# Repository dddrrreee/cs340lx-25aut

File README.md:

### CS340lx: (even more) advanced systems labs

Official description:
  - This is an implementation-heavy, lab-based class that continues the
    topics from CS240LX. The labs will be more specialized, with an emphasis
    on research-worthy topics and techniques. The class format will follow
    CS240LX: two labs, twice a week, along with a set of research papers
    for context.

Context:
 - Final class in the 140e/240lx pipeline (as of rn :).
 - We only offer it every few years when there is an unusual 
   group.  Lots of great alumni!
 - This is the 3rd offering.
 - Joe graduated, but we have Joseph as a variant!

Structure:
 - 140e and 240lx have to fulfill class requirements, so content somewhat
   constrained.  
 - 340lx we build whatever seems interesting --- only rule is we build and
   you have a working example of a cool trick or deep method every lab.

   In general: we go broader on fun stuff (devices), go deeper on
   interesting stuff than the simple examples in previous labs.  
 - One fantastic difference: Around half of the labs are usually
   student-written.  You have already suffered through over 30 labs
   as consumers, so now is your chance to buld the labs you would have 
   wanted.  

   This is my favorite part of the class.  I always learn alot.  The new
   labs give tricks useful for 140e/240lx.  And, as we saw, (eg Stuart's
   elf lab) these labs can >>> better than our staff ones :)

What's the big picture goal: 
 - Do a bunch of cool devices for fun.  

   Since we have a limited enrollment, can afford more expensive ones
   (lidar, screens, kilometer capable LoRa RF)

 - Do a bunch of new sbc's --- arm, riscv, whatever.  

   Often bootup is
   the most difficult part, so it's good to have a portfolio.  Also once
   you see more, you start to get a feel for what is an arbitrary choice

   and which have a
 - Now that you have a solid grasp of low-level hardware and code, we 
   build more advanced stuff, and go much deeper.    

   From the past: build a riscv simulator that can simulate itself and
   is register equivalent with the hardware.

 - Build simple versions of advanced techniques in other areas.
   Some examples from the past:
     - Build a SAT solver (Matthew)
     - Build a constraint solver (Matthew)
     - Static analysis bug finders (Matthew and Manya),
     - Verilog FPGA examples (Zack)

-------------------------------------------------------------------
### Possible labs

Definite lab:
 - Parthiv's PCB lab next thursday 10/2.

Some possible good labs from 240lx final projects

 - Stuart's elf debug: use to make a real profiler.
 - Quake (sai and james): will do screen and keyboard labs
 - ox64 (Aditya et al): cheap, real riscv
 - Pi zero 2 (Benji): 4 armv7 processor, faster, still bcm2835.
 - handwriting rec (Chia-Hsiang, Irene, Kaylee, Weixin)
 - fuse?

Likely devices:
  - i2s microphone, 
  - class D amplifier + speaker
  - HDMI screen
  - Lidar
  - camera?
  - sbcs: pico 2, pico, ox64, pi zero 2

Tentative things I'd like to do (won't do all)
     - Doing Turing complete DMA (based on Max Cura's hack) - Speed up
     interrupts/exceptions by 50x.
  - a solid network boot loader that works over RF, sound, light, IR.
    It's wild to send code using sound or a blinky light.
  - A few projects putting together several devices.
    (e.g., accel controlled lights, acoustically reactive displays)
    Key: use tricks to verify the system so you're suprised if it breaks.
  - in honor of Joe: chip8 video game emulator.
  - Make a bunch of stuff really, really fast.  Fun hack is write code
    on your pi that beats
    linux/macos on your fancy modern laptop --- e.g., exceptions or 
    tiny processes so you can quickly fork 100,000 (versus crashing 
    your laptop).
  - finally build the runtime tools we were discussing: eraser race detector, 
    volatile checker.
  - do much better versions of 140e labs so can pull them in: ideally
    a simple complete OS.  definitely a better fast FAT32

The basic play: we've spend a couple quarters learning alot of low-level
stuff the hard way.  Now reap the rewards using it to build the cool
stuff.

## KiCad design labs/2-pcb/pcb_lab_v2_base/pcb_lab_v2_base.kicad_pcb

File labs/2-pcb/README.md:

# PCB (KiCAD) Lab v2 by Parthiv

## Overview
This lab will be focused on designing printed circuit boards (PCBs), which many students in 140e/240lx/340lx have found useful over the years in final projects to help reduce wiring complexity and increase hardware reliability. The focus of the lab will be on how to replace a bundle of wires with an inexpensive PCB, and not on how to actually design electrical circuits (which is a much more complicated discussion). For the most part, you can get by just connecting breakout boards together. If you want to integrate a piece of hardware without a breakout board, most datasheets will include an "application circuit" that will show you what supporting hardware is needed.

Our goal is to create a board that can plug into the Raspberry Pi GPIO header and connect to a USB to UART converter along with some RGB LEDs. To extend the lab, you'll also add in connections to a few sensors/peripherals/hardware of your choice. 

## General Keyboard Shortcuts
I assume `Ctrl` becomes `Cmd` on mac.

* `Ctrl+S`: Save (do often!)
* `Ctrl+Z`: Undo
* `Ctrl+Y`: Redo

## Step 0: Prelab

Please review [PRELAB.md](./PRELAB.md). If interested, you can also check out a previous version of the lab [here](https://github.com/dddrrreee/cs240lx-23spr/tree/main/labs/16-pcb). In the original version of the lab, we focused on designing a board with NRF24L01 wireless transceivers. You can use that board for inspiration if you'd prefer to do something a little more "batteries included".

**A mouse will be very helpful!**

## Step 1: Creating a Project

1. Open up KiCAD (either type `kicad` in your terminal or search for it in your installed applications).
2. Go to File->New Project. Select a location where you want to create the project (you can do it in this directory) and give it a name. Ensure that the box to "Create a new folder for the project" is selected. Create the project.
3. You should see a window like this:

    On the left side, you can see a file called [project_name].kicad_pcb and another file called [project_name].kicad_sch. Double clicking these will open the PCB and Schematic editors respectively. We will learn what these are in more detail.

## Step 2: Creating a Schematic

1. In the main KiCAD window, double click the .kicad_sch file to open the Schematic editor. You'll probably get a popup saying that KiCAD is being run for the first time; just use the default option to "Copy default global symbol library table". Once that's done, you will see a blank schematic:

    The schematic is where we will describe what pins of what components connect to what other pins of other components. The analog here is your `.h` file. You'll definine the connections between components (like function interfaces) but not the actual physical implementation of those connections (like the function implementations in `.c`). You should try to keep this organized if you can! I will show you some strategies on how to do this. 

    You can middle click and drag to move, or scroll up/down to zoom. Ctrl+scroll will move you left/right and shift+scroll will move you up and down, if you prefer that to middle click and drag.

2. Go to Place->Add Symbol (or type the keyboard shortcut `A`). Again, if you get a popup here, "Copy default global footprint library". In the search bar, search for the symbol `Raspberry_Pi_2_3`. Select it, then click OK to start placing the component. Place it somewhere in the middle of the schematic by clicking. If you want to move it, you can click on it, hit `M`, and then move it around, then click again to place it. You'll immediately notice that the pins are laid out quite differently from the actual physical pins on the Pi. And you'll see just one GND, 5V, and 3.3V pin, though the Pi has many. This is one of the ways that we simplify the schematic view to make it a bit easier to see what's going on. In older versions of KiCAD, you may see all of the power pins represented; if so, you can just wire them all together in the schematic (see old version of the lab).

3. Now, we will connect the power rails of the Raspberry Pi. Hit `P` to open up the power symbol menu. Search for `GND`, select it, and hit OK to start placing the ground symbol. Put it near the bottom of the Raspberry Pi symbol. Hover over the end of one of the GND pins on the Pi, then hit `W` to start drawing a wire. Note that it'll start drawing a wire from wherever your mouse was; if it was in a bad spot, you can click `Esc` to cancel drawing the wire and try again. Connect the Pi's GND pin to the GND symbol you just placed.

    Next, add power symbols for `+5V` and `+3V3` to the schematic, and connect those to the 5V and 3V3 pins of the Pi.

4. Now that we've connected the power for the Pi, let's add the RGB LEDs. We are going to use the SK6812 LEDs, which are compatible with the more common WS2812 but work with the 3.3V logic level that the Pi outputs. Technically, WS2812 require 5V logic (though we often get away with 3.3V for small chains). You can review the SK6812 datasheet in [docs/SK6812.pdf](docs/SK6812.pdf). It's a pretty short datasheet and worth looking through the whole thing.

    In the schematic view, type `A` to add a new component, then search for `SK6812`. Place a few of them down (however many you'd like)! You can also just place one, click `Esc` to get out of the add component mode, then left click and drag to select the LED you placed, then Ctrl+C/Ctrl+V to duplicate it however many times. 
    
    Something to know is VDD (or sometimes VCC) in datasheets or component pinouts refers to the positive voltage, while VSS (or VEE) refers to ground.
    
    If you read the datasheet (read the datasheet!), you'll see that the manufacturer recommends placing capacitors between the 5V supply and ground near each of the LEDs. This is a pretty common thing you'll see to help provide a more stable voltage supply to more power-hungry components. Usually, they'll specify the capacitance properly (in pF, uF, or nF), but here you can see a 3-number code of `104`. A quick search will tell you that `104` is 100nF or 0.1uF. Let's add these capacitors too; the name in the parts menu is `C`.
    
    Go ahead and connect +5V and GND sources to each of the LEDs as required (type `P` to add power sources, `W` to draw wires). When drawing wires, if you click before reaching your destination, you'll get to decide where the wire turns in the schematic view which can be helpful for organization. It's common to just have a whole bunch of power sources all over the schematic to avoid drawing long wires between them. There is an implied connection between all sources with the same label. 

    Pro-tip: you can make one LED/capacitor/wires/sources unit and then copy/paste that a few times. 

    Apply the capacitance value to the capacitors by clicking on the capacitor, then typing `E` to edit. Then in the popup window, update the value in the `Value` field. This isn't enforced in any way, it's just a note so you know what it is when you're placing the capacitors on the PCB.

    Choose a Pi pin to connect the first LED's DIN port to. I chose GPIO12 (which is incidentally pin 32). Your schematic should look something like this:

5. Now, let's create a connector for a [USB/UART converter breakout board](https://www.amazon.com/MTDELE-CP2102-Serial-Adapter-Module/dp/B0D76NNWVW) so we can plug it directly into the PCB. Unfortunately, most breakout boards won't have an associated symbol in KiCAD, but it's good practice for creating new symbols. We'll want to create a symbol to represent the logical pins that the USB/UART has. Go to Tools->Symbol Editor. You will see a blank symbol editor like this:

    On the left, you can see various symbol libraries which contain different default parts that are common enough to be included in KiCAD. We will be creating a new one.

    In the symbol editor, go to File->New Library. If you make it Project, any parts you make will only be usable in the current project. If you make it Global, you can use it in future projects. I went with Project but either is ok. Give it whatever name you want (`cs340lx_pcb`, or something).

    On the left window, find the library you created and right click on it. Then click New Symbol, and you'll see a new window pop up. See below for recommended settings.

    Click on OK and create it. 
    
    On the left of the main window (to the right of the list of libraries), right click on the grid and select Edit Grids.

    In the window that shows up, change the Fast Grid Switching: Grid 1 to 100mil/2.54mm. This helps with alignment for placing pins in the symbol. Then close this window, and type `Alt+1` to switch to the 100mil/2.54mm grid. Make sure the bottom of the symbol editor shows `grid 100`.
    
    Now that setup is done, it's time to make the symbol. On the right side of the main window, select the Draw Rectangles tool and draw a rectangle on the screen. Don't worry, you can change it later. If you want to move the auto-generated text (`J`), you can click on it (press escape to reach select mode like in the schematic editor) and hit `M` to move it. Click to place.

    Now, we will add the pins. Hit `P` to create a pin. We'll make the `GND` pin, which is pin number 4 (4th from the top of the UART) and is a Power Output. The reason we choose Output is because the entire system's power/ground is going to be generated by the UART plugged into your computer.

    Place the pin down at the bottom of the rectangle, ensuring that the circle end of the pin is facing out (this is where you'll connect wires in the schematic). Click `R` to rotate the pin.

    Create the remaining 4 pins:

    - 1: 3V3, power output
    - 2: TX, output
    - 3: RX, input
    - 4: GND, power output (already did in step 11)
    - 5: 5V, power output

    Try to keep voltage at the top, ground at the bottom, and signals on the sides (like the Raspberry Pi symbol). You can grow and shrink the rectangle if needed by going to the select tool (escape) and then clicking on the border of the recctangle. Your symbol should look something like this (doesn't have to match exactly). You can rotate a pin with `R` and move with `M` like you'd expect.

    You can add text using the text tool on the right side. Once you've finished the UART symbol, save with Ctrl-S or Command-S, then exit the symbol editor. In the schematic editor, click `A` to add a symbol. Search for the UART you just created; you should see it pop up.

    Connect the 5V pin to your +5V rail, GND to GND, TX to the Pi RX and RX to the Pi TX. You can optionally connect 3V3 to +3V3, but this isn't strictly necessary since the Pi also creates its own 3V3 on the pins. I left it unconnected.

    By convention, if wires appear to cross but don't have a circle over the intersection, they are considered to NOT be connected.

    Hover over an unused pin on the Pi and hit `Q` to mark it as a No-Connect (looks like an X). This declares that you meant to not connect this pin and didn't just forget to connect it. Now, you're in no-connect placing mode and you can click on all the unused pins on the Pi/LEDs/UART/your custom hardware. Compare your schematic against the Completed Schematic section below, making sure that everything is connected the way it should be.

6. Create and add new symbols for your selected sensors of choice. If you used breakout boards, there should be very little/no additional supporting hardware and you should just be able to wire up to pins on the Pi. You can check datasheets or hookup guides to be sure. Feel free to ask Parthiv for help/confirmation. Make sure your pins are numbered correctly, which will make things much easier later on.

7. Annotate the schematic with `Tools->Annotate Schematic`. A window will pop up, click Annotate, which assigns reference designators (`C1`, `J2`, etc) to all the symbols. Click `Close`.

8. Now, go to `Inspect->Electrical Rules Checker` and click Run ERC to run the ERC. Make sure you annotate the schematic first; otherwise, you get a ton of weird errors. This is like a type checker in software; it will catch violations of electrical rules (type rules) but NOT correctness. And sometimes it rejects valid schematics (like a type checker can reject valid programs), which you will see.

    You will hopefully see 0-1 errors. If you connected the UART 3V3 to +3V3, you will not get the error I have. This error is because whoever made the Raspberry Pi Symbol decided to make the 3V3 pin a power input even though it's a power output. So the ERC thinks nobody is providing power to +3V3. We know this to be wrong (the Pi outputs 3V3) so we can ignore this.

    If you have other errors, address them and re-run ERC. A common error is forgetting to put a no-connect on a pin that is unconnected. Also, be careful with custom symbols that you properly assigned the pin types.

9. The last step is to assign footprints, which are the representation of each symbol in the real world PCB. Go to `Tools->Assign Footprints`, which will open a new window. 

    You will see that the LEDs have footprints already assigned. It's worthwhile to check the datasheet to make sure these are correct. We need to assign footprints for the other components. Click on the row with C1, then on the left side look for library `Capacitor_SMD` (capacitor, surface mount device). On the right side, look for footprint `Capacitor_SMD:C_0603_1608Metric`. This corresponds to a standard 0603 surface mount capacitor, which is a super common size. Double click on `Capacitor_SMD:C_0603_1608Metric`, which will assign that footprint to our capacitor.

    Go through and do this for all the components:

    - Both capacitors: `Capacitor_SMD:C_0603_1608Metric`
    - Pi: Library `Connector_PinSocket_2.54mm`, footprint `Connector_PinSocket_2.54mm:PinSocket_2x20_P2.54mm_Vertical` (0.1" female header, 2x20)
    - UART: Library `Connector_PinSocket_2.54mm`, footprint `Connector_PinSocket_2.54mm:PinSocket_1x05_P2.54mm_Horizontal` (0.1" female 90 degree header, 1x5).
    - Your selected breakout boards: probably a 2.54mm 1xN PinSocket for some N.

    Then click "Apply, Save Schematic & Continue". You can then close out of the Assign Footprints window and the schematic editor.

### Schematic Editor Keyboard Shortcuts

* `A`: add symbol
* `P`: add power symbol
* `Esc`: go to regular mouse (select) mode
* `M`: move (after selecting a symbol)
* `R`: rotate (after selecting a symbol)
* `E`: edit symbol properties (after selecting a symbol)
* `Q`: place no-connect symbol (should be in select mode first)
* `W`: draw wire (should be in select mode first)

### Schematic Editor Tools

* Tools->Symbol Editor: create new symbols
* Tools->Annotate Schematic: assign reference designators
* Tools->Assign Footprints: assign PCB footprints to schematic symbols
* Inspect->Electrical Rules Checker: validate against some rules

### Symbol Editor Keyboard Shortcuts

* `P`: add pin
* `Esc`: go to regular mouse (select) mode
* `M`: move (after selecting a symbol)
* `R`: rotate (after selecting a symbol)your Schematic 

## Step 2: Laying out the PCB

Time to create the PCB! For all of these steps, you don't have to match the exact thing I do. Actually better if you don't, so it's your board and not you making my board :D

1. From the KiCAD main window, double click the .kicad_pcb file to open the PCB editor. You will see a blank PCB, this time a black background instead of white (schematic).

    You can middle click and drag to move, or scroll up/down to zoom. Ctrl+scroll will move you left/right and shift+scroll will move you up and down, if you prefer that to middle click and drag.

2. Go to Tools->Update PCB From Schematic. This will open a window, click "Update PCB". You should do this any time you edit your schematic or assign new footprints in the schematic.

    Hopefully, there are zero warnings/errors. A common error is forgetting to assign a footprint to a symbol in the schematic. If you do this, then KiCAD is unsure what physical footprint to assign to the logical symbol you created in the schematic. Revisit step 19 from part 1 if this happens. Then, come back to the PCB viewer and this step again.

    If you have zero warnings/errors, then you can "Close" the window that popped up, and then click anywhere to place the mess of components.

    You will see a 2x20 pin header for the Pi, 1x5 header for the UART, LEDs, capacitors, and any additional headers/components for your chosen hardware.

    If you look at the picture at the very top of this page, you will see that the Pi header is on the underside of the board whereas everything else is on the top. To move the Pi connector to the backside of the board, click on it, then hit `F` to "flip" it to the back. You will see the outline change from pink to blue, and also the text related to the Pi header will be mirrored. 

    You can also go to View->3D viewer to see this, though there will probably be an error about not having a board outline yet (which we will fix shortly).

3. Now, we will try to organize the components reasonably well to minimize the length of the connections we need to make. Hit `Esc` to go to select mode, then click on any footprint. Once you've selected the footprint, you can rotate it with `R` or move it with `M`. Click to place when you're in move mode. 

    All of the thin lines you see connecting the different pins of components are connections we will eventually need to make, so trying to keep these as "untangled" as possible will make things easier. That being said, it's probably impossible to completely avoid crossing (it's not an issue to have crossing wires as we can route wires on the front and back of the board).

    I would recommend putting the Pi header at the top of the other components, with the +5V pads to the left. Then, put the UART near the left side of the Pi header (so there's a short path for +5V).

    Also, make sure to keep each capacitor close to the +5V pad of one of the LEDs. Technically, the way that our schematic is, we could connect them to anywhere on +5V and GND. However, we would like to keep the resistance on the path between the capacitor and the LED as small as possible, so that the capacitor can deliver power to the LED when it has current spikes when turned on bright. Here's one possible arrangement which is pretty reasonable:

    You'll see I assigned the wrong footprint for the UART (not a Horizontal/right angle header) so I went ahead and fixed that in the Schematic editor (Tools->Assign Footprints) then went back to the PCB editor and ran Tools->Update PCB from Schematic.

    If you're particular about alignment, you can select multiple components with Shift-Click and then right click. In the menu, select "Align/Distribute" and mess around till you get what you want. 

4. Now let's draw our board outlines. On the right side, you will see a bunch of Layers

    These each represent a different layer of the PCB. Some highlights:
    * `F` and `B` prefixes are for front and back, as we can have many things on either side of the board
    * `Cu`: front and back copper, which are where we make our connections. In a more-than-2 layer board, we will have `In1.Cu`, `In2.Cu`, etc.
    * `Adhesive`: some components are glued to the board, this layer shows where the glue should be placed
    * `Paste`: for surface-mount components, this is where the machine will automatically place solder paste. After components are automatically placed in their locations, the whole board is baked, melting the solder paste, then cooled, hardening the paste (and making electrical/mechanical connection with the components).
    * `Silkscreen`: text/drawings that are printed on the board for aesthetic/documentation reasons
    * `Mask`: The green (or other color) layer of the board which protects the underlying copper from corrosion and accidental shorts. It's expected that most of the board has mask, so the `Mask` layer is actually the negative. So it shows where there is _not_ mask.
    * `User.*`: these don't get printed, so you can put stuff for documentation
    * `Edge.Cuts`: the edges of the board which are cut.
    * `Courtyard`: bounding polygons for the various components. Ideally, no courtyards overlap so we can ensure that no components are inside each other. Just like we had an ERC in schematic, we have a DRC (design rules check) for the PCB which will complain if two courtyards overlap. However sometimes we know that we are safe (e.g. capacitor fits "under" NRF).

    You can enable/disable the visibility of layers by clicking the eye icon, which can be interesting. 

    You'll want to click on the `Edge.Cuts` layer and make sure the triangle is pointing to it (like in the image above). Select the rectangle tool (also selected in the image above). Now, draw a rectangle around the components you made by clicking once for one corner, then clicking again for the opposite corner. Give yourself some extra space for routing traces (wires) around the components. 

    Now, if you open View->3D Viewer, you will see your new outline.

    If you make it too big/too small, you can always edit this by clicking on the `Edge.Cuts` layer, then the select tool (`Esc`), then clicking on the corner of the rectangle and changing the shape. 

    You can also make a custom shape using a vector graphics tool like inkscape, then export as SVG. Then go to File->Import->Graphics and add your shape to the `Edge.Cuts` layer.

5. A common practice in PCB design is to make (almost) the entire front of the board be connected to your power rail, and (almost) the entire back of the board be connected to your ground rail (or vice versa). This helps you avoid having to manually connect every power and ground together, sort of like how we just connected them to the GND and +5V symbols on the schematic to avoid a ratsnest of wires between the power pins.

    We will do that now. Click on the `F.Cu` layer and do `Ctrl+Shift+Z` (mac may be `Cmd` instead of `Ctrl`) to open a window for "copper zone". Ensure that the `F.Cu` layer is selected on the left, then select the `+5V` net.

    Hit OK, then draw a rectangle that's bigger than the rectangle you drew for the edge cuts (this time, you need to click all 4 corners, not just 2 opposite). Repeat the process for `B.Cu` and `GND`. It should look something like this when you're done:

    If you mess up while you're drawing, you can hit `Esc` and try again.

6. Let's actually fill the zones to make the electrical connections. Hit `B` to fill zones. This should hopefully connect all of our +5V and GND connections for us! You'll see the connection lines for those disappear. If you zoom in to some pins, you will see what exactly happened:

    Notice that on the front side (red), where we made the 5V zone, KiCAD helpfully connected the pin with an X pattern. On the back side (blue), where we made the GND zone, KiCAD connected with an X pattern. It may be easier to see what's going on if you make one of the two copper layers invisible (see above). Make sure to turn it back on afterwards.

7. Now the fun begins: time to route our traces! Click on `F.Cu` on the left to route on the front of the board. Then, select a `1 mm` trace width. Move your mouse over the +5V pad on the UART (you can zoom with scroll wheel, and middle click+drag to pan). Hit `X` to enter trace mode. If you move your mouse, you will see a trace expanding out of the pad. 

    Each time you click in trace mode, you will "save" some of your progress that you've made. Once you reach your target, you can click on it to finish routing the trace. In general, try to avoid 90 degree turns. 

    Go ahead and connect the Pi pin you selected for the LED signal to the first LED. It's ok to go in between the pins of the Pi. Then, hit `B` to re-fill the zones, and you'll see a bit of the front +5V zone has been cleared out to allow the trace you just made to go through it. 

    Let's now route the other 2 UART connections. I started doing that, but it seems like my traces will have to cross!

    We have a few options on how to solve this. We can go all the way around with one of the connections.

    But you'll notice this cut off the Pi's +5V pins from the rest of the +5V zone, making an "island". KiCAD is drawing a short connection line between the main zone and the "island" to inform us of this. We could go ahead and connect this, but it's not ideal.

    We have two layers! We could, for example, just cross the signals by moving one to the back of the board. While routing one of the signals (with `X`), click `V` to enter Via mode, and then place the Via somewhere so you can swap sides of the board. Since the UART Module uses through-hole pins, it can connect directly on the backside to the backside trace. Surface mount components (like our LEDs and capacitors) can only connect on the side they're placed on, so you'd need another via to bring the signal back to the front.

    We can also just route the whole signal on the back of the board. If you're not currently routing any trace (`Esc`), then clicking `V` will swap you between the front and the back. If you're on the back, the board will appear blue. 

    This is a bit of a contrived/silly example, but hopefully it demonstrates that you have a lot of options available when routing more complicated netlists. You may have to experiment with different solutions to problems and backtrack if things get too complicated. An absolute worst case scenario is to go a 4-layer board. It just increases cost (though not by a lot if you are ok with all your vias going all the way through the board). Most projects you'd do should be routable on 2 layers.

8. Finish up routing the surface mount components. You'll notice that the GND pins on the LEDs and capacitors cannot connect to the GND plane on the back; this is because they are surface mount components and only connect to the front by default. Add vias for those, either by starting a routing with `X` and then hitting `V` to place a via, or by hitting `Ctrl+Shift+X` to place a via directly. After placing the via and selecting the GND net, you can then route.
    
    Finish up routing your custom hardware, then save (hopefully you've been doing this throughout). You can admire your work in the View->3D Viewer!

9. I would recommend adding some annotations on the Silkscreen. You can click the `F.Silkscreen` (or `B.Silkscreen`) on the right side, then the text tool, and add annotations. At the very least, it's good to write the pin names on the various connectors (or at least enough that you plug it in the right way). And label the different connectors if you have several.

    My completed base PCB:

10. Almost done with the board! Let's run DRC (design rules checker) which will make sure our board is manufacturable. Go to Inspect->Design Rules Checker. In the window that pops up, enable "Test for parity between PCB and schematic" just to be sure.

Click Run DRC. If you have errors, go to the DRC Errors section below for common errors. For each, I'd recommend you zoom in super close, then click the entry in the DRC window. You will see an arrow in the middle of your screen. Address the issue and then click Run DRC in the window again. If there are other errors, ask me and I can help you out. 

### Routing Tips

#### Clearance
Try to give clearance to pads and don't route traces too close to them (especially ones that connect to planes). This makes it easier in the future to route signals from those pads.

#### Try, try, try again

Don't be afraid to delete an old trace and re-route it if you find you need to move it to make something else work.

#### Zone Islands
An extremely common issue that people ran into was creating a filled zone "island", like below: 

Notice how the two traces have created an almost closed-loop, which cuts off a section of the filled zone into an island that's disconnected from the rest. An easy fix is to open the closed loop by moving one or more of the segments of the traces onto the other layer. If you go to the select mode (`Esc`), then click on a piece of trace, then hit `E`, then swap the layer to the other layer. You can then go and place vias (`Ctrl+Shift+V`, or `Opt+V` for mac?) on each end of the segment that you flipped to the other side to make electrical connection.

Another (worse) solution is to to put a via on the island and off the island and route a "jump" on the other side of the board. This isn't really recommended though, since it means there is higher resistance on the power plane (vias introduce resistance).

### DRC Errors

Here are some common DRC errors/warnings

#### Track has unconnected end

You have some track that is only connected on one side and can just be deleted. A tricky one is when the track is contained entirely inside a pad hole, so it's invisible (see below). Just click on the exact tip of the arrow that is pointing out the error and it should get highlighted. Then just hit `Del`. It helps to be VERY zoomed in on the PCB editor window.

#### Silkscreen clipped by solder mask

You have silkscreen that is either drawn off the edge of the board, or overlaps a pad somehow. Either expand your board (go to `Edge.Cuts` layer, then `Esc` to select, then click and expand the rectangle). Or move the silkscreen item (go to appropriate `*.Silkscreen` layer, then `Esc` to select, then click item, then `M` to move it). Below you can see I drew my board too small so the silkscreen hangs off the edge.

### PCB Editor Keyboard Shortcuts
* `Esc`: go to regular mouse (select) mode
* `M`: move (after selecting a footprint)
* `R`: rotate (after selecting a footprint)
* `F`: flip footprint (after selecting a footprint)
* `Ctrl+Shift+Z` (or `Opt+Z` on Mac?): create filled zone
* `B`: fill zones
* `X`: route trace
* `V`: swap active copper layer (front to back or vice versa)
* `Ctrl+Shift+V` (or `Opt+V` on Mac?): create via
* `E`: edit properties
* `Ctrl+Shift+T` (or `Opt+T` on Mac?): add text (in silkscreen layer)

### PCB Editor Tools
* Tools->Update PCB From Schematic: Apply any updates from the schematic editor (make sure to save in schematic editor)
* View-3D Viewer: view a 3D model of your board
* Inspect->Design Rules Checker: validate that it's manufacturable

## Step 3: Manufacture the PCB

Coming soon. If you get to this point and it's not ready, refer to a previous lab. I just need to dry run and make sure that everything is still the same. 

## Step 4: Extensions

Here are some ideas for extensions.

1. Rather than using a CP2102 breakout board, look up a datasheet and place your own CP2102 chip and all of the various supporting components so you can plug a USB cable into your PCB and talk UART with your Pi. You can also check out the included `parthiv_pcb_v2.1` project which will contain a sub-schematic for the CP2102N and supporting hardware. You can copy this schematic into your project and import it, though it's a good exercise to build it from a datasheet. 

2. You can also do the same with any raw part that you selected, which will often be much cheaper than doing it with the breakout for volume production. However, I would always suggest having the breakout board as a backup option to help you determine if bugs are software-related or hardware-related. Check out JLCPCB parts to see what's available for manufacturing.

3. Create some interesting artwork and integrate it into the board shape, silkscreen, and/or component layout of your board.

4. Use the [KiCAD python API](https://gitlab.com/kicad/code/kicad-python) to programatically define aspects of your layout. For example, you can place a bunch of LEDs into a grid.

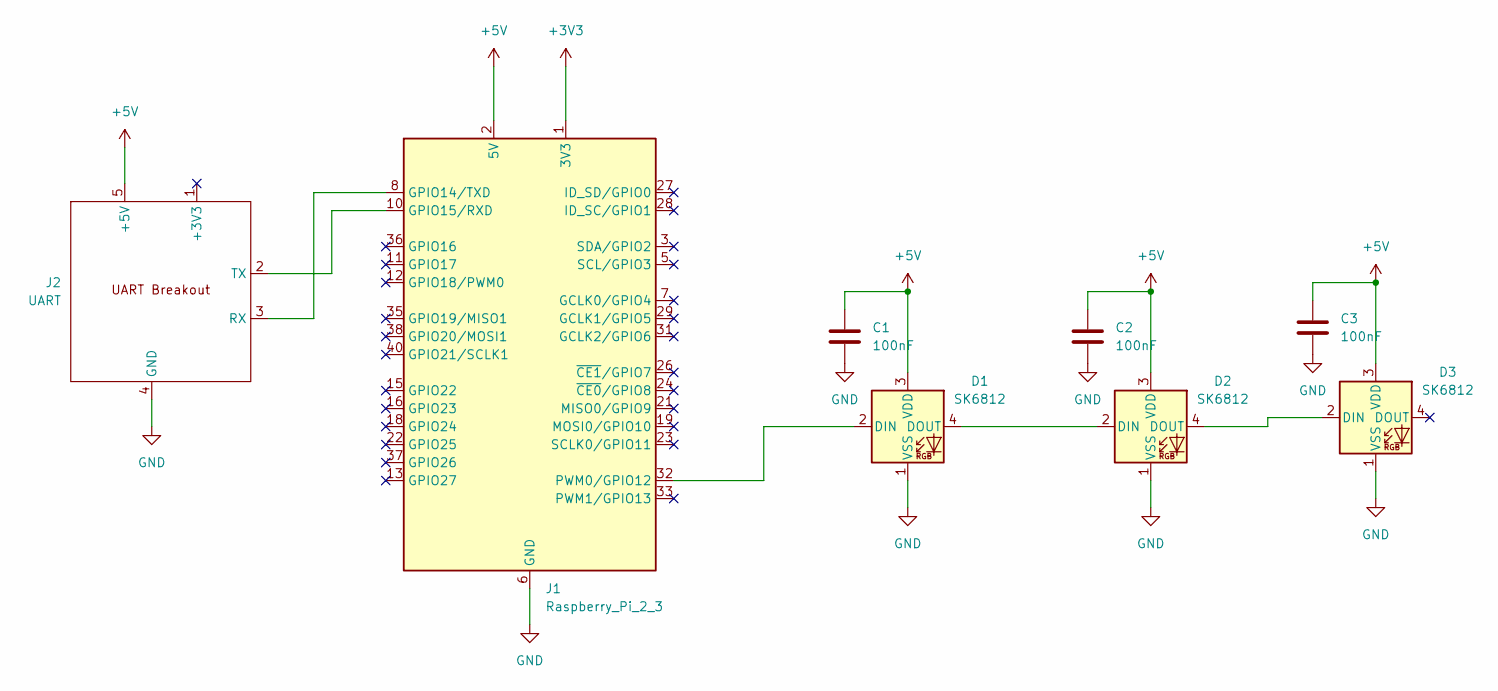
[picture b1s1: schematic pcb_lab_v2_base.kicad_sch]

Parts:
C1, C2, C3: 100nF; C_0603_1608Metric
D1, D2, D3: SK6812; LED_SK6812_PLCC4_5.0x5.0mm_P3.2mm
J1: Raspberry_Pi_2_3; PinSocket_2x20_P2.54mm_Vertical
J2: UART; PinSocket_1x05_P2.54mm_Vertical

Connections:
+3V3: J1.1 (3V3), J1.17 (3V3)
+5V: C1.1, C2.1, C3.1, D1.3 (VDD), D2.3 (VDD), D3.3 (VDD), J1.2 (5V), J1.4 (5V), J2.5 (+5V)
GND: C1.2, C2.2, C3.2, D1.1 (VSS), D2.1 (VSS), D3.1 (VSS), J1.6 (GND), J1.9 (GND), J1.14 (GND), J1.20 (GND), J1.25 (GND), J1.30 (GND), J1.34 (GND), J1.39 (GND), J2.4 (GND)
unnamed: D1.2 (DIN), J1.32 (PWM0/GPIO12)
unnamed: D1.4 (DOUT), D2.2 (DIN)
unnamed: D2.4 (DOUT), D3.2 (DIN)
unnamed: J1.8 (GPIO14/TXD), J2.3 (RX)
unnamed: J1.10 (GPIO15/RXD), J2.2 (TX)

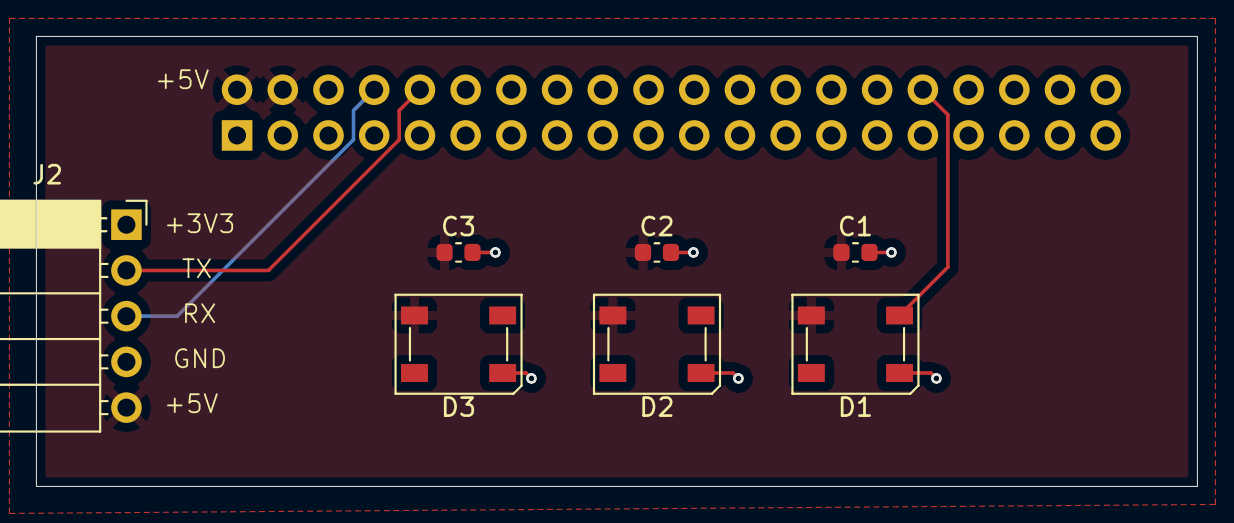
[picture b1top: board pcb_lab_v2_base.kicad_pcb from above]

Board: 2 copper layers, 64.5 x 25.0 mm, 8 parts (1 on the bottom side), 8 nets.

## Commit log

2025-09-23 minor
2025-10-07 added lidar
2025-10-21 dev order
2025-10-28 more
2025-11-11 added irene's lab
2025-11-13 Bluetooth lab
2025-11-13 Improve printk
2025-11-13 Fix circular queue
2025-11-13 Add gpio-high
2025-11-13 Point to gpio-high
2025-11-13 Update readme images
2025-11-13 Readme improvements
2025-11-13 Additional README figure
2025-11-13 Fixed staff-pl011.o
2025-11-13 BT lab improvements
2025-11-13 BT minor
2025-11-13 README spelling
2025-11-21 fixed
2025-12-02 camera first commit
2025-12-02 clean
2025-12-02 half
2025-12-02 lab 12 new commit
2025-12-02 add readme
2025-12-03 README complete
2025-12-03 correct readme
2025-12-03 final
2025-12-03 fix makefile typo
2025-12-03 README minor update
2025-12-05 new lab
